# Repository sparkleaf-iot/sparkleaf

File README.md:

# sparkleaf

Sparkleaf is about connecting tapping into the plant electrophysiology using ESP32's.

Using Nomad and Consul to deploy container based microservices. Currently only works on GCP.

## Components

### Nomad

Nomad config can be found in deployment/config folder and jobs in deplyoment/jobs.

### Consul

Consul for service discovery, tightly bound to nomad and deployed in a similar fashion.

### Traefik

Traefik as a reverse proxy deployed in nomad using the docker container. Traefik configuration is in the job file under /jobs.

### Pulumi

Pulumi in golang for IaC, see main.go

### Packer

Despite relying on containers for the actual application, a base image is created for vm's that have Consul/Nomad preinstalled. Speeds up boot and scaling. See image.pkr.hcl for details.

## Deployment

Deployment requires a GCP account and credentials and pulumi installed on the local machine. Cd into /deployment and pulumi up should be the only necessairy step. Consul UI can be found on serverip:8500 and nomad on :4646. Traefik dashboard is on clientip:8081.

Beware that currently an existing managed DNS zone in GCP is necessary. Change 'sparkleaf-main' to whatever your zone is called in the main.go file.

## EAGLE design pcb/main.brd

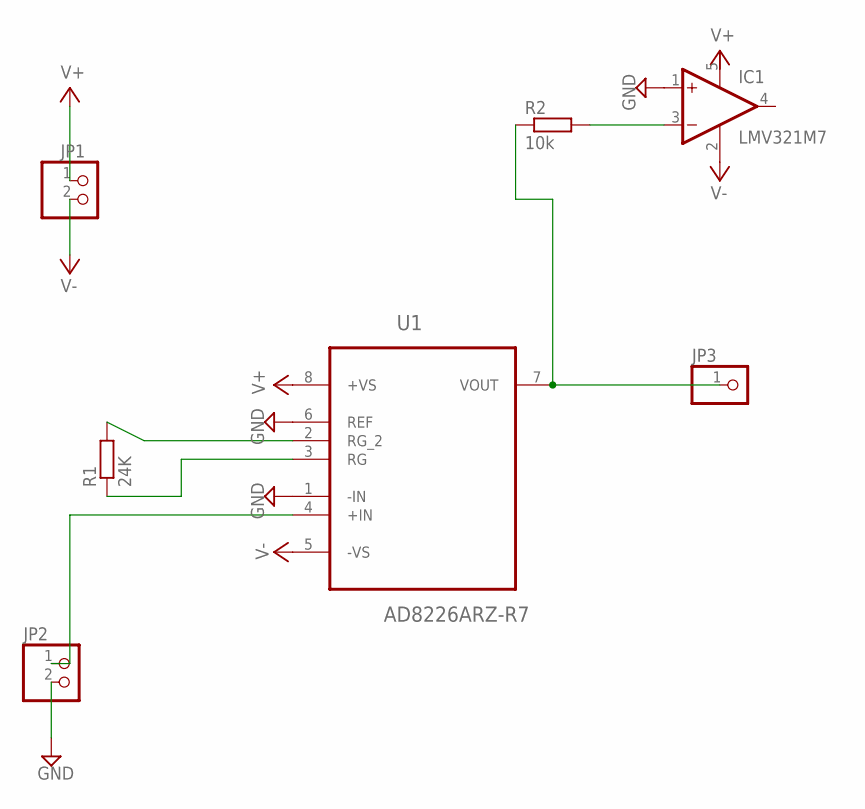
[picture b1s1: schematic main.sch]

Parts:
IC1: LMV321M7; SC70-5L
JP1, JP2: PINHD-1X2; 1X02
JP3: PINHD-1X1; 1X01
R1: 24K; R0805
R2: 10k; R0805
U1: AD8226ARZ-R7; SOIC127P600X175-8N

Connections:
GND: IC1.1 (+IN), JP2.2, U1.1 (-IN), U1.6 (REF)
unnamed: R1.2, U1.2 (RG_2)
unnamed: R1.1, U1.3 (RG)
unnamed: JP2.1, U1.4 (+IN)
unnamed: IC1.3 (-IN), R2.2
unnamed: JP3.1, R2.1, U1.7 (VOUT)
V+: IC1.5 (V+), JP1.1, U1.8 (+VS)
V-: IC1.2 (V-), JP1.2, U1.5 (-VS)

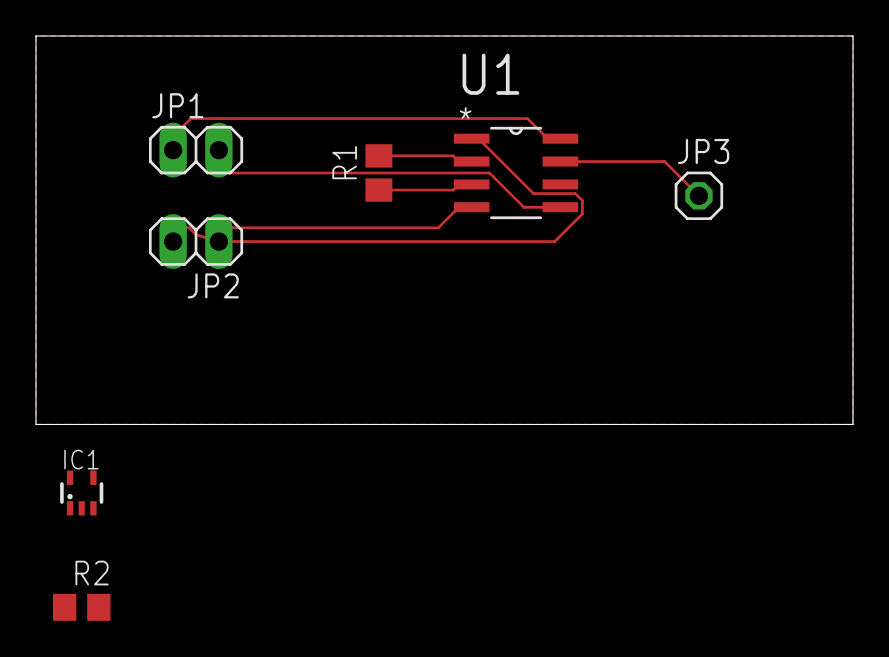
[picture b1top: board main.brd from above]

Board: 2 copper layers, 45.4 x 21.6 mm, 7 parts (0 on the bottom side), 8 nets.

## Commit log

2022-11-14 added general handler for all incoming req
2022-11-14 added dockerfile for handler
2022-11-14 Update Dockerfile
2022-11-15 fixed dockerfile
2022-11-17 changed port to 80
2022-11-17 changed port on deployment and added service
2022-11-17 reverted port to 8080
2022-11-18 added infrastructure diagram
2023-04-02 added jobs and conf to nomad
2023-04-04 added pulumi base setup
2023-04-04 added basic nomad provisionning in pulumi
2023-04-04 added cluster creation to nomad
2023-04-09 added firewall, and subnet to main
2023-04-12 fixed mistakes in pulumi deployment main file
2023-04-17 working: reverted to only intance + network
2023-04-19 added packer to build gce image
2023-04-20 fixed packer script crash
2023-04-20 removed subnet and change to autosubnetcreation in network
2023-04-24 added server startup script
2023-04-25 added mandatory config for server client and nomad itself
2023-04-26 added consul to config
2023-05-02 added token generation and injection for acl access
2023-05-03 added token export to local file on vm
2023-05-04 fixed server script to properly read token
2023-05-08 added nomad auto join config and acl roles
2023-05-09 fixed client auto join consul
2023-05-09 export client/server hostnames to hosts
2023-05-15 added consul kv request to fetch token
2023-05-17 added traefik job
2023-05-18 removed old files and deleted commented out code
2023-05-18 removed old dockerfile
2023-05-18 removed dockerfile
2023-05-19 added csi node and controller
2023-05-23 added volume to iac definition
2023-05-25 added service account key creation
2023-05-26 added kv call
2023-05-28 added volume creation
2023-05-29 added role to service account
2023-05-29 added influx port to fw
2023-06-08 added k6 sample test
2023-06-09 added explicit advertise to nomad config
2023-06-12 added waitforleader
2023-06-13 reset bootstrap_expect to 1
2023-06-13 added individual startup tokens for each instance to kv
2023-06-16 increased bootstrap expect to 3 again
2023-06-17 commented out jobs
2023-06-17 nomad bt but not writing to consul kv
2023-06-24 fixed server script
2023-06-25 rebuilt and fixed issue
2023-06-28 added traefik and influxdb services to consul
2023-06-30 changed traefik to system task
2023-06-30 added dynamic record sets to dns zone
2023-07-02 added recordset for influx subdomain
2023-07-02 added k6 test
2023-07-05 added preview workflow
2023-07-05 fixed folder location
2023-07-05 changed file name
2023-07-05 added permissions to workflow
2023-07-05 fixed stack name
2023-07-05 added workdir
2023-07-06 changed wi pool
2023-07-07 added utilgo
2023-07-09 added aruino files
2023-07-11 cleaned files
2023-07-11 Added PCB files
